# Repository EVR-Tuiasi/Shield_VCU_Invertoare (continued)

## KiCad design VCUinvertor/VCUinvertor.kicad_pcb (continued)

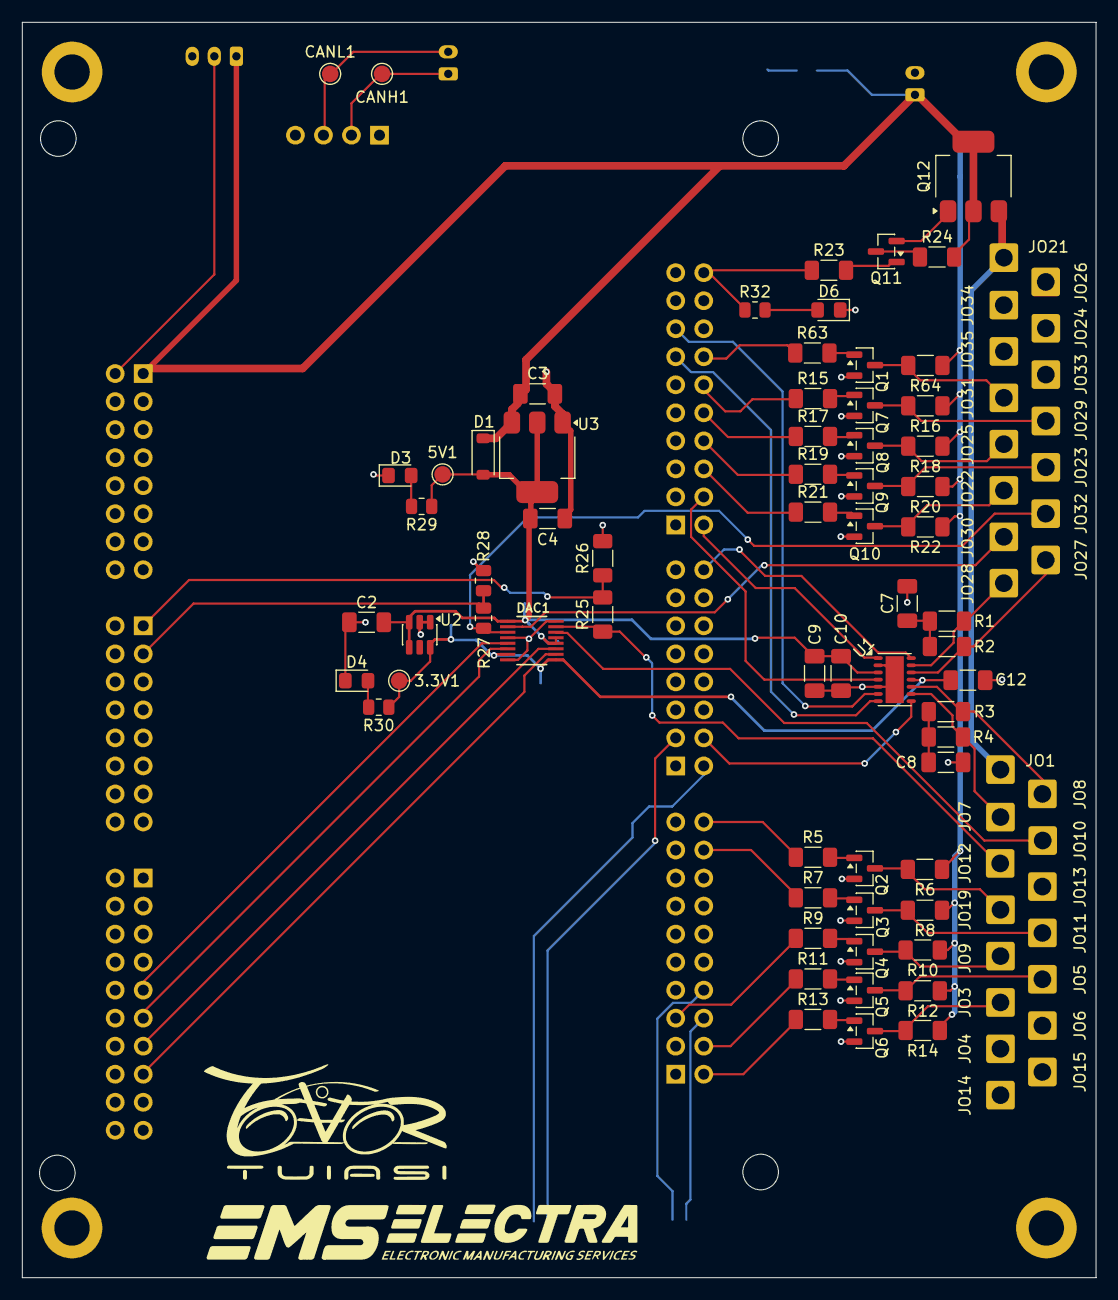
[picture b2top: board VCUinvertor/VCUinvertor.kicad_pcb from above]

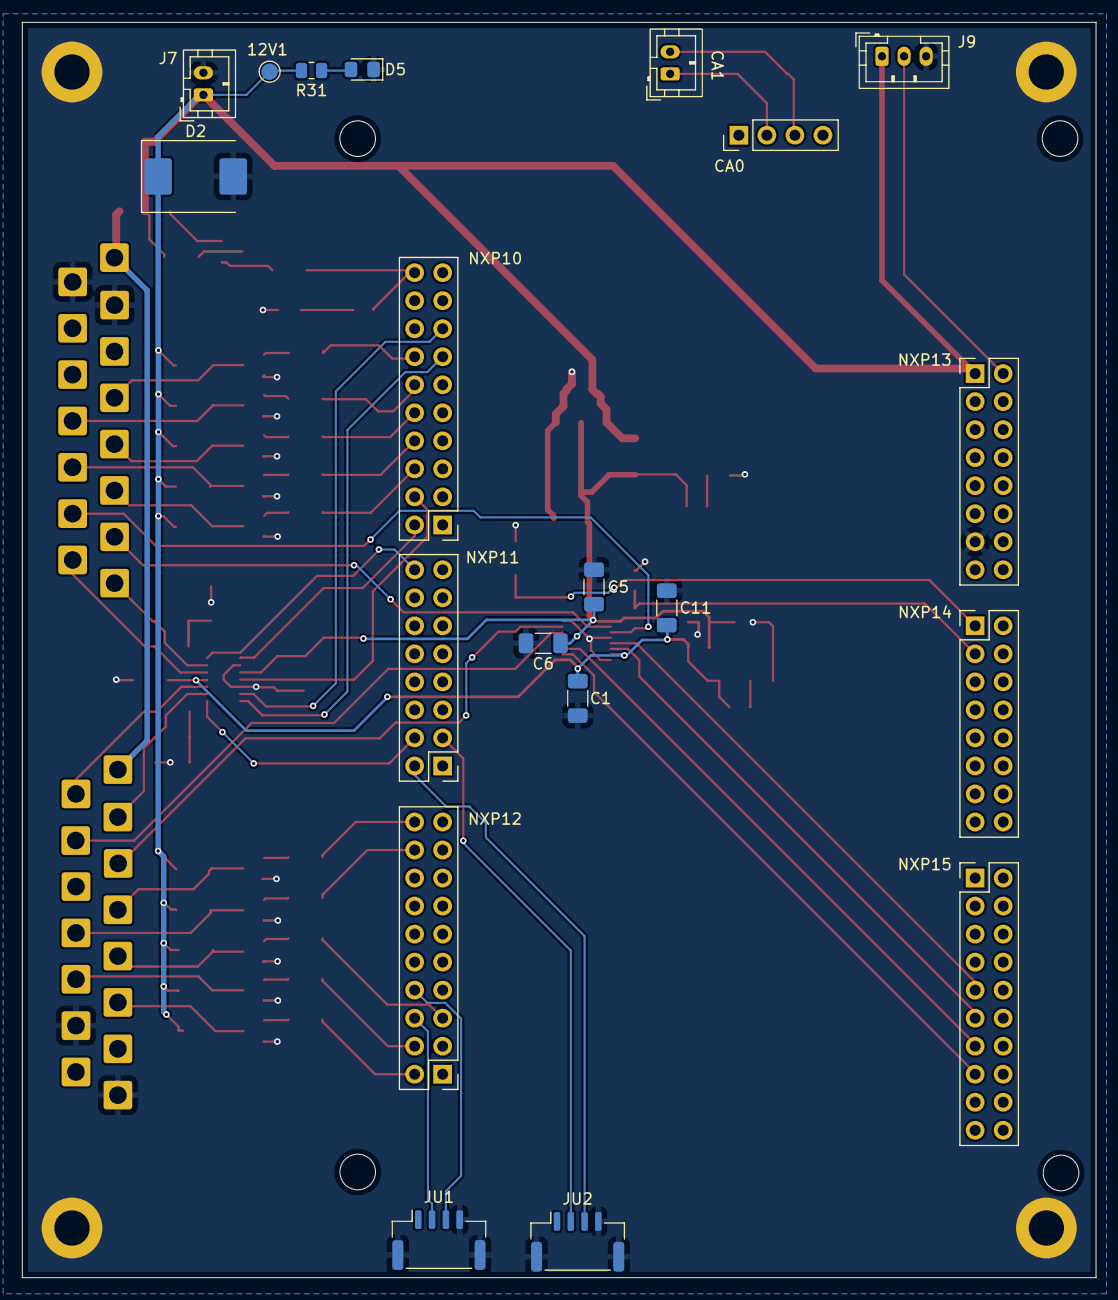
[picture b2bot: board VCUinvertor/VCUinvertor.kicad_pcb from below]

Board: 2 copper layers, 97.3 x 113.8 mm, 119 parts (20 on the bottom side), 72 nets.

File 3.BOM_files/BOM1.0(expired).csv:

Reference,Qty,Value,DNP,Exclude from BOM,Exclude from Board,Footprint,Datasheet
"C1,C2,C3,C5,C6,C10,C12",7,0.1uF,,,,Capacitor_SMD:C_0805_2012Metric_Pad1.18x1.45mm_HandSolder,~
C4,1,2.2uF,,,,Capacitor_SMD:C_0805_2012Metric_Pad1.18x1.45mm_HandSolder,~
"C7,C8",2,4.7uF,,,,Capacitor_SMD:C_0805_2012Metric_Pad1.18x1.45mm_HandSolder,~
"C9,C11",2,10uF,,,,Capacitor_SMD:C_0805_2012Metric_Pad1.18x1.45mm_HandSolder,~
CA0,1,CAN_NXP,,,,Connector_PinHeader_2.54mm:PinHeader_1x04_P2.54mm_Vertical,~
CA1,1,CAN_OUT_NXP,,,,Connector_JST:JST_PH_B2B-PH-K_1x02_P2.00mm_Vertical,~
D1,1,MBR0540,,,,Diode_SMD:D_SOD-123,http://www.mccsemi.com/up_pdf/MBR0520~MBR0580(SOD123).pdf
D2,1,MBRS340,,,,Diode_SMD:D_SMC,https://www.onsemi.com/download/data-sheet/pdf/mbrs340t3-d.pdf
DAC1,1,LTC2645HMS-L12_PBF,,,,LTC2645HMS-L12_PBF:MSOP-16_MS,
"H1,H2,H3,H4",4,MountingHole_Pad,,Excluded from BOM,,MountingHole:MountingHole_3.2mm_M3_ISO14580_Pad,~
J7,1,PowerSupply,,,,Connector_JST:JST_PH_B2B-PH-K_1x02_P2.00mm_Vertical,~
J9,1,BREAKLIGHT,,,,Connector_JST:JST_PH_B3B-PH-K_1x03_P2.00mm_Vertical,~
"JO1,JO21",2,PWR (Pink),,,,Connector_Wire:SolderWire-0.75sqmm_1x01_D1.25mm_OD2.3mm,~
"JO3,JO22",2,REV (Orange),,,,Connector_Wire:SolderWire-0.75sqmm_1x01_D1.25mm_OD2.3mm,~
"JO4,JO15,JO24,JO35",4,12V (Red),,,,Connector_Wire:SolderWire-0.75sqmm_1x01_D1.25mm_OD2.3mm,~
"JO5,JO23",2,FWD (White),,,,Connector_Wire:SolderWire-0.75sqmm_1x01_D1.25mm_OD2.3mm,~
"JO6,JO14,JO26,JO34",4,GND (Black),,,,Connector_Wire:SolderWire-0.75sqmm_1x01_D1.25mm_OD2.3mm,~
"JO7,JO27",2,CAN_L (Brownish),,,,Connector_Wire:SolderWire-0.75sqmm_1x01_D1.25mm_OD2.3mm,~
"JO8,JO28",2,CAN_H (Greenish),,,,Connector_Wire:SolderWire-0.75sqmm_1x01_D1.25mm_OD2.3mm,~
"JO9,JO25",2,H_Brk (Yellowish),,,,Connector_Wire:SolderWire-0.75sqmm_1x01_D1.25mm_OD2.3mm,~
"JO10,JO30",2,Brk_AN (Brown),,,,Connector_Wire:SolderWire-0.75sqmm_1x01_D1.25mm_OD2.3mm,~
"JO11,JO29",2,ECO (Blue),,,,Connector_Wire:SolderWire-0.75sqmm_1x01_D1.25mm_OD2.3mm,~
"JO12,JO32",2,TPS (Green),,,,Connector_Wire:SolderWire-0.75sqmm_1x01_D1.25mm_OD2.3mm,~
"JO13,JO33",2,5V (Purple),,,,Connector_Wire:SolderWire-0.75sqmm_1x01_D1.25mm_OD2.3mm,~
"JO19,JO31",2,ACC (Gray),,,,Connector_Wire:SolderWire-0.75sqmm_1x01_D1.25mm_OD2.3mm,~
JU1,1,UART_INV01,,,,Connector_JST:JST_GH_SM04B-GHS-TB_1x04-1MP_P1.25mm_Horizontal,~
JU2,1,UART_INV02,,,,Connector_JST:JST_GH_SM04B-GHS-TB_1x04-1MP_P1.25mm_Horizontal,~
NXP10,1,NXP10,,,,Connector_PinHeader_2.54mm:PinHeader_2x10_P2.54mm_Vertical,~
NXP11,1,NXP11,,,,Connector_PinHeader_2.54mm:PinHeader_2x08_P2.54mm_Vertical,~
NXP12,1,NXP12,,,,Connector_PinHeader_2.54mm:PinHeader_2x10_P2.54mm_Vertical,~
NXP13,1,NXP13,,,,Connector_PinHeader_2.54mm:PinHeader_2x08_P2.54mm_Vertical,~
NXP14,1,NXP14,,,,Connector_PinHeader_2.54mm:PinHeader_2x08_P2.54mm_Vertical,~
NXP15,1,NXP15,,,,Connector_PinHeader_2.54mm:PinHeader_2x10_P2.54mm_Vertical,~
"Q1,Q2,Q3,Q4,Q5,Q6,Q7,Q8,Q9,Q10",10,2N7002,,,,Package_TO_SOT_SMD:SOT-23,https://www.onsemi.com/pub/Collateral/NDS7002A-D.PDF
Q11,1,BC848C,,,,Package_TO_SOT_SMD:SOT-23,http://www.infineon.com/dgdl/Infineon-BC847SERIES_BC848SERIE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
Q12,1,BCP51,,,,Package_TO_SOT_SMD:SOT-223-3_TabPin2,https://www.onsemi.com/pub/Collateral/BCP51-D.pdf
"R1,R2,R3,R4",4,60R4,,,,Resistor_SMD:R_0805_2012Metric,~
"R5,R6,R7,R8,R9,R10,R11,R12,R13,R14,R15,R16,R17,R18,R19,R20,R21,R22,R26,R28,R63,R64",22,10k,,,,Resistor_SMD:R_0805_2012Metric,~
R23,1,1.7k,,,,Resistor_SMD:R_0805_2012Metric,~
R24,1,360R,,,,Resistor_SMD:R_0805_2012Metric,~
"R25,R27",2,5.1k,,,,Resistor_SMD:R_0805_2012Metric,~
U1,1,TJA1448ATK,,,,Package_DFN_QFN:DFN-14-1EP_3x4.5mm_P0.65mm_EP1.65x4.25mm,https://www.nxp.com/docs/en/data-sheet/TJA1145.pdf
U2,1,REF3433T,,,,Package_TO_SOT_SMD:SOT-23-6,https://www.ti.com/lit/ds/symlink/ref35.pdf
U3,1,TLV76150DCY,,,,Package_TO_SOT_SMD:SOT-223-3_TabPin2,https://www.ti.com/lit/ds/symlink/tlv761.pdf

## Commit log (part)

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2026-03-26 Scheme added
2026-03-27 Layout_Invertor2
2026-03-28 NMOS_Simulation_Selection
2026-03-28 Footprint assignment
2026-03-29 Layout_Global arrangement
2026-03-29 DAQ footprint correction
2026-03-30 New PMOS config for switching
2026-03-30 VCU_PinCorrection_0.1
2026-03-30 Pin_Assignment_Main_Done
    [15:48, 3/30/2026] Viorel VCU: ptb22 - j12 - pin 1 - LPUART1_TX - UART_INV01 pin 3
    ptb23 - j12 - pin 3 - LPUART1_RX - UART_INV01 pin 2
    ptd2 - j11 - pin 5 - LPUART3_TX - UART_INV02 pin 3
    ptd3 - j11 - pin 7 - LPUART3_RX - UART_INV01 pin 2
    [15:55, 3/30/2026] Viorel VCU: pte23 - j15 - pin 9 - EMIOS1_CH3_H - PWM_NXP1
    pte24 - j15 - pin 11 - EMIOS1_CH4_H - PWM_NXP2
2026-03-30 FirstLayout_Completed
2026-03-31 Pyy & Pzz pin assignment
2026-03-31 Added datasheets for MOS
2026-04-01 LastCorrection_ToBeChecked
2026-04-01 Logo_added
2026-04-01 Block diagram cleanup
2026-04-01 BOM csv added
2026-04-04 Changes on Supply
    1.Protection shottky diode added
    2.Separate supply for INV via Darlington (1A Max.)
    3.Control of the supply from J10 Pin 20 for INV supply - added
2026-04-04 BOM + Gerbers - added
2026-04-06 SMD components resized for Handsoldering (0805 -> 1206)
    *Resistors & Capacitors are now upgraded to size 1206 for easy handsoldering
2026-04-06 Gerber for bigSMD added
2026-04-07 TestPoints added
2026-04-07 Ref LEDs added
    For 3.3V & 5V & ...
    Added for easy testing, LEDs running 2-3 mA each
2026-04-07 Folders_smallManagement
2026-04-08 DAC1 - 3D model added
2026-04-24 Corrections on UART01/02
2026-04-26 Board - resized + Hole corrections
2026-04-27 INV wires displacement change
    Some connections were brought closer to their control pin
2026-04-27 Corrections wiring Brake_light
2026-04-28 Redid layout for CAN and DAC chips
2026-04-28 CleanUp after changes
2026-04-28 12V -> BAT+
2026-04-29 DAC - cap location correction
2026-04-29 History file ignored
2026-04-29 Redid reverse polarity protection
2026-04-29 Supply GND small correction
2026-04-30 Dorlington -> Relay for INV_OFF
2026-05-09 Simulations_continued
2026-05-11 Relay NC to NO change
2026-05-11 Changes on NXPTPSOUT1&2
    1. Switch The switch to NO from NC --> From pin 2 to pin 4
    2.Move the connectors of the TPS OUT1 & 2
2026-05-11 Error corrections - Done
2026-05-13 Small drawing correction
2026-05-14 STEP file added
2026-05-18 MOS pulldown + missing INV pins added
2026-05-19 Wire labels correction
2026-05-26 Revision author added
2026-06-01 Corrections + PUMP&FAN circuit 0.1
2026-06-01 PCB Layout with FAN&PUMP MOS - Done
2026-06-03 Hole_mounting displacement correction
2026-06-04 INV pinout+ layout changes - Done
2026-06-04 Board silkscreen corrections for visibility
2026-06-05 FAN&PUMP pin change
2026-06-06 Pin - GND assignment
2026-06-06 Check on BC848C
2026-06-07 Mounting Holes + Relay Flyback added
2026-06-08 Connectors 2.0mm -> 2.5mm correction
2026-06-10 FAN MOS correction D->S
2026-06-14 Gate Driver MOS added + layout done
2026-06-14 CAN_IN + CAN_OUT added
2026-06-17 Prototype tested for FAN control
2026-06-20 TEMP/PRESSURE ctrl schematic - proto
2026-06-21 CAN: TJA1448 Footprint correction
2026-06-21 Changed resistor footprints to 1206
2026-06-22 BOM - added
2026-06-23 Small optimisations, added jumper for CAN transciever VIO
2026-06-23 Thickened traces for fans, pumps and inverter supply
2026-06-23 Redid connection for pump and fan signals
2026-06-23 Fixed violation for unconnected pin
2026-06-23 Updated BOM, two components left
2026-06-23 Changed the LED to be the same as VCU_Board
2026-06-23 Removed components that we have already from BOM
2026-06-25 Redid connections for pressure and temperature sensors
2026-06-25 LDO supply wire correction
2026-06-25 GBR - added
2026-06-26 Remove custom GND for protection
2026-06-29 GND plane small correction + new GBR - added + sent
